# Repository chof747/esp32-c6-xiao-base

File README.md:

# Base battery board setup for a esp32-c6 xiao

Use this project to create an esp32-c6 module with battery power using the battery connectors on the xiao chip.

## Contains

- ESP32 C6 Xiao module
- 2.54 space battery pin connector
- Voltage sensing

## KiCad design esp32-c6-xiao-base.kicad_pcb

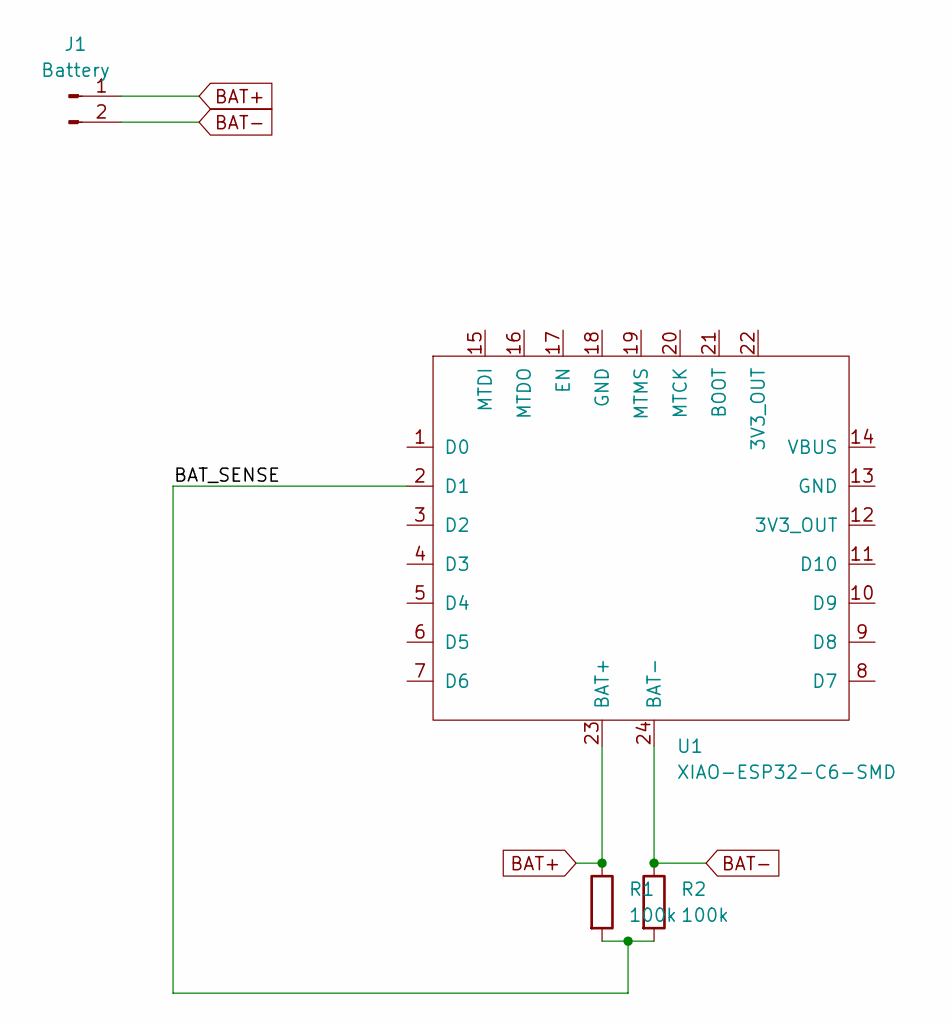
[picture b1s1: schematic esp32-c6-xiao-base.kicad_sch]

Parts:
J1: Battery; PinHeader_1x02_P2.54mm_Horizontal
R1, R2: 100k; R_0603_1608Metric_Pad0.98x0.95mm_HandSolder
U1: XIAO-ESP32-C6-SMD; XIAO-ESP32-C6-DIP

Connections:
/BAT_SENSE: R1.2, R2.2, U1.2 (D1)
BAT+: J1.1, R1.1, U1.23 (BAT+)
BAT-: J1.2, R2.1, U1.24 (BAT-)

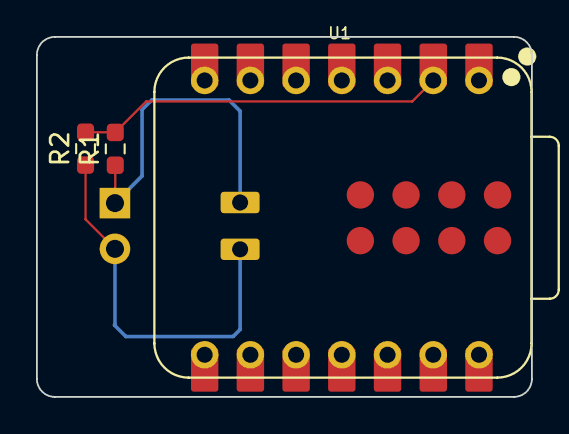
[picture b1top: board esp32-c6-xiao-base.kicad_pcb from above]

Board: 2 copper layers, 27.5 x 20.0 mm, 4 parts (1 on the bottom side), 3 nets.
